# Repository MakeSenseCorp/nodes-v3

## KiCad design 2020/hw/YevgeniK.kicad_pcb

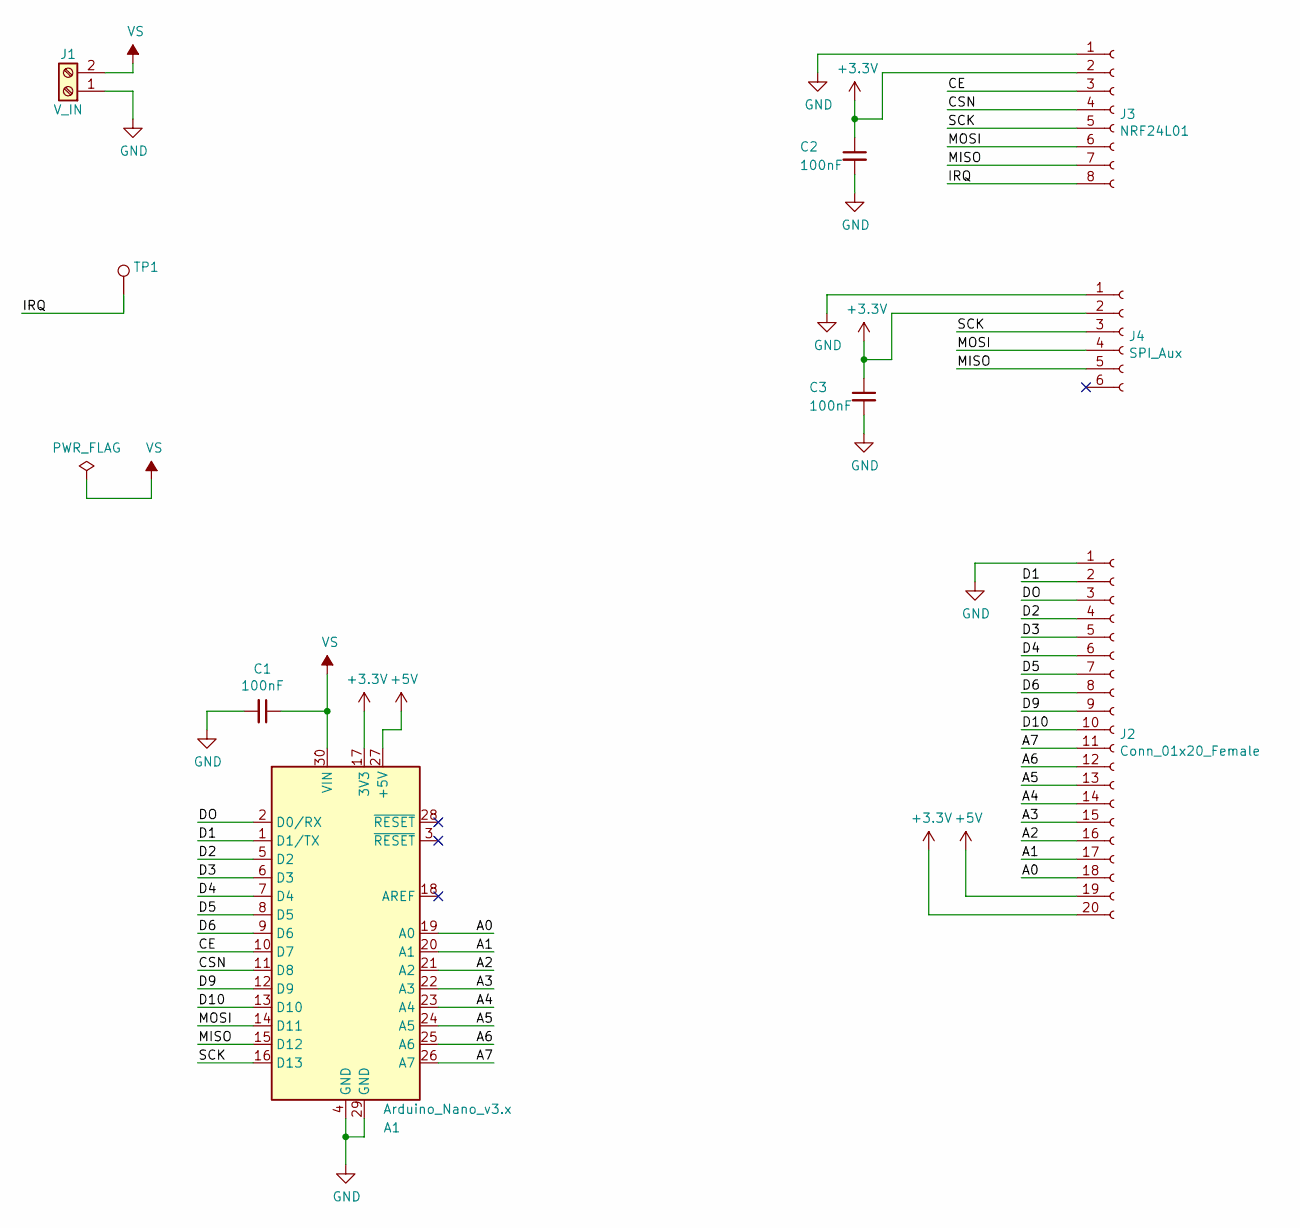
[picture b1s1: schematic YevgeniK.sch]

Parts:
A1: Arduino_Nano_v3.x; Arduino_Nano
C1, C2, C3: 100nF; C_0805_2012Metric
J1: V_IN; TerminalBlock_bornier-2_P5.08mm
J2: Conn_01x20_Female; PinHeader_1x20_P2.54mm_Vertical
J3: NRF24L01; PinHeader_2x04_P2.54mm_Vertical
J4: SPI_Aux; PinHeader_1x06_P2.54mm_Vertical
TP1: TestPoint; TestPoint_Pad_D2.0mm

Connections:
+3V3: A1.17 (3V3), C2.1, C3.1, J2.20, J3.2, J4.2
+5V: A1.27 (+5V), J2.19
/A0: A1.19 (A0), J2.18
/A1: A1.20 (A1), J2.17
/A2: A1.21 (A2), J2.16
/A3: A1.22 (A3), J2.15
/A4: A1.23 (A4), J2.14
/A5: A1.24 (A5), J2.13
/A6: A1.25 (A6), J2.12
/A7: A1.26 (A7), J2.11
/CE: A1.10 (D7), J3.3
/CSN: A1.11 (D8), J3.4
/D1: A1.1 (D1/TX), J2.2
/D2: A1.5 (D2), J2.4
/D3: A1.6 (D3), J2.5
/D4: A1.7 (D4), J2.6
/D5: A1.8 (D5), J2.7
/D6: A1.9 (D6), J2.8
/D9: A1.12 (D9), J2.9
/D10: A1.13 (D10), J2.10
/DO: A1.2 (D0/RX), J2.3
/IRQ: J3.8, TP1.1
/MISO: A1.15 (D12), J3.7, J4.5
/MOSI: A1.14 (D11), J3.6, J4.4
/SCK: A1.16 (D13), J3.5, J4.3
GND: A1.4 (GND), A1.29 (GND), C1.2, C2.2, C3.2, J1.1, J2.1, J3.1, J4.1
VS: A1.30 (VIN), C1.1, J1.2

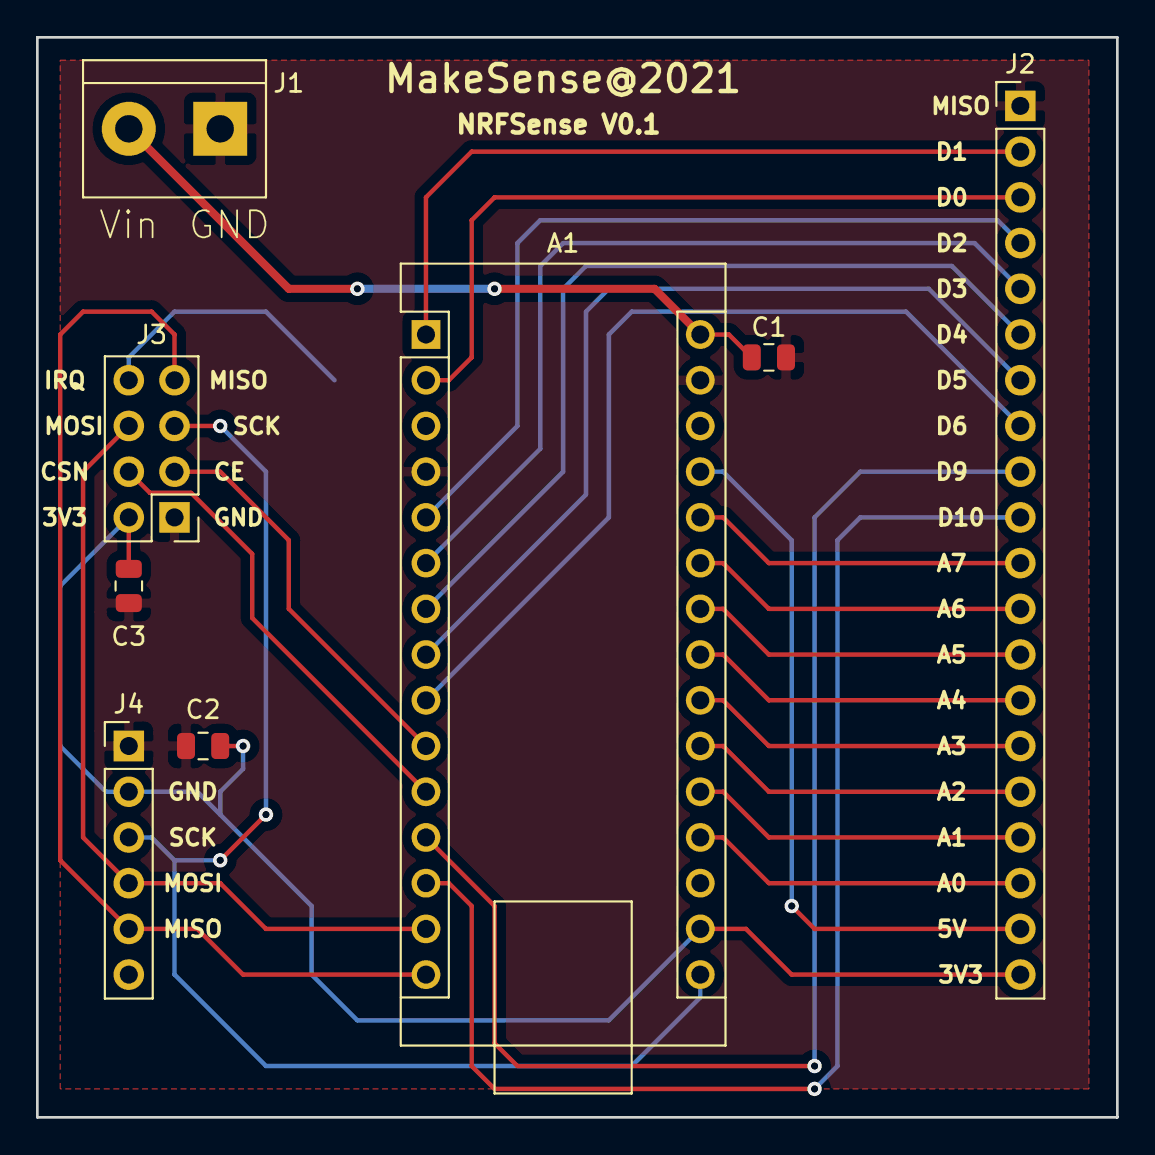
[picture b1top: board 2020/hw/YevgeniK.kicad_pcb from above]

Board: 2 copper layers, 60.0 x 60.0 mm, 9 parts (1 on the bottom side), 27 nets.

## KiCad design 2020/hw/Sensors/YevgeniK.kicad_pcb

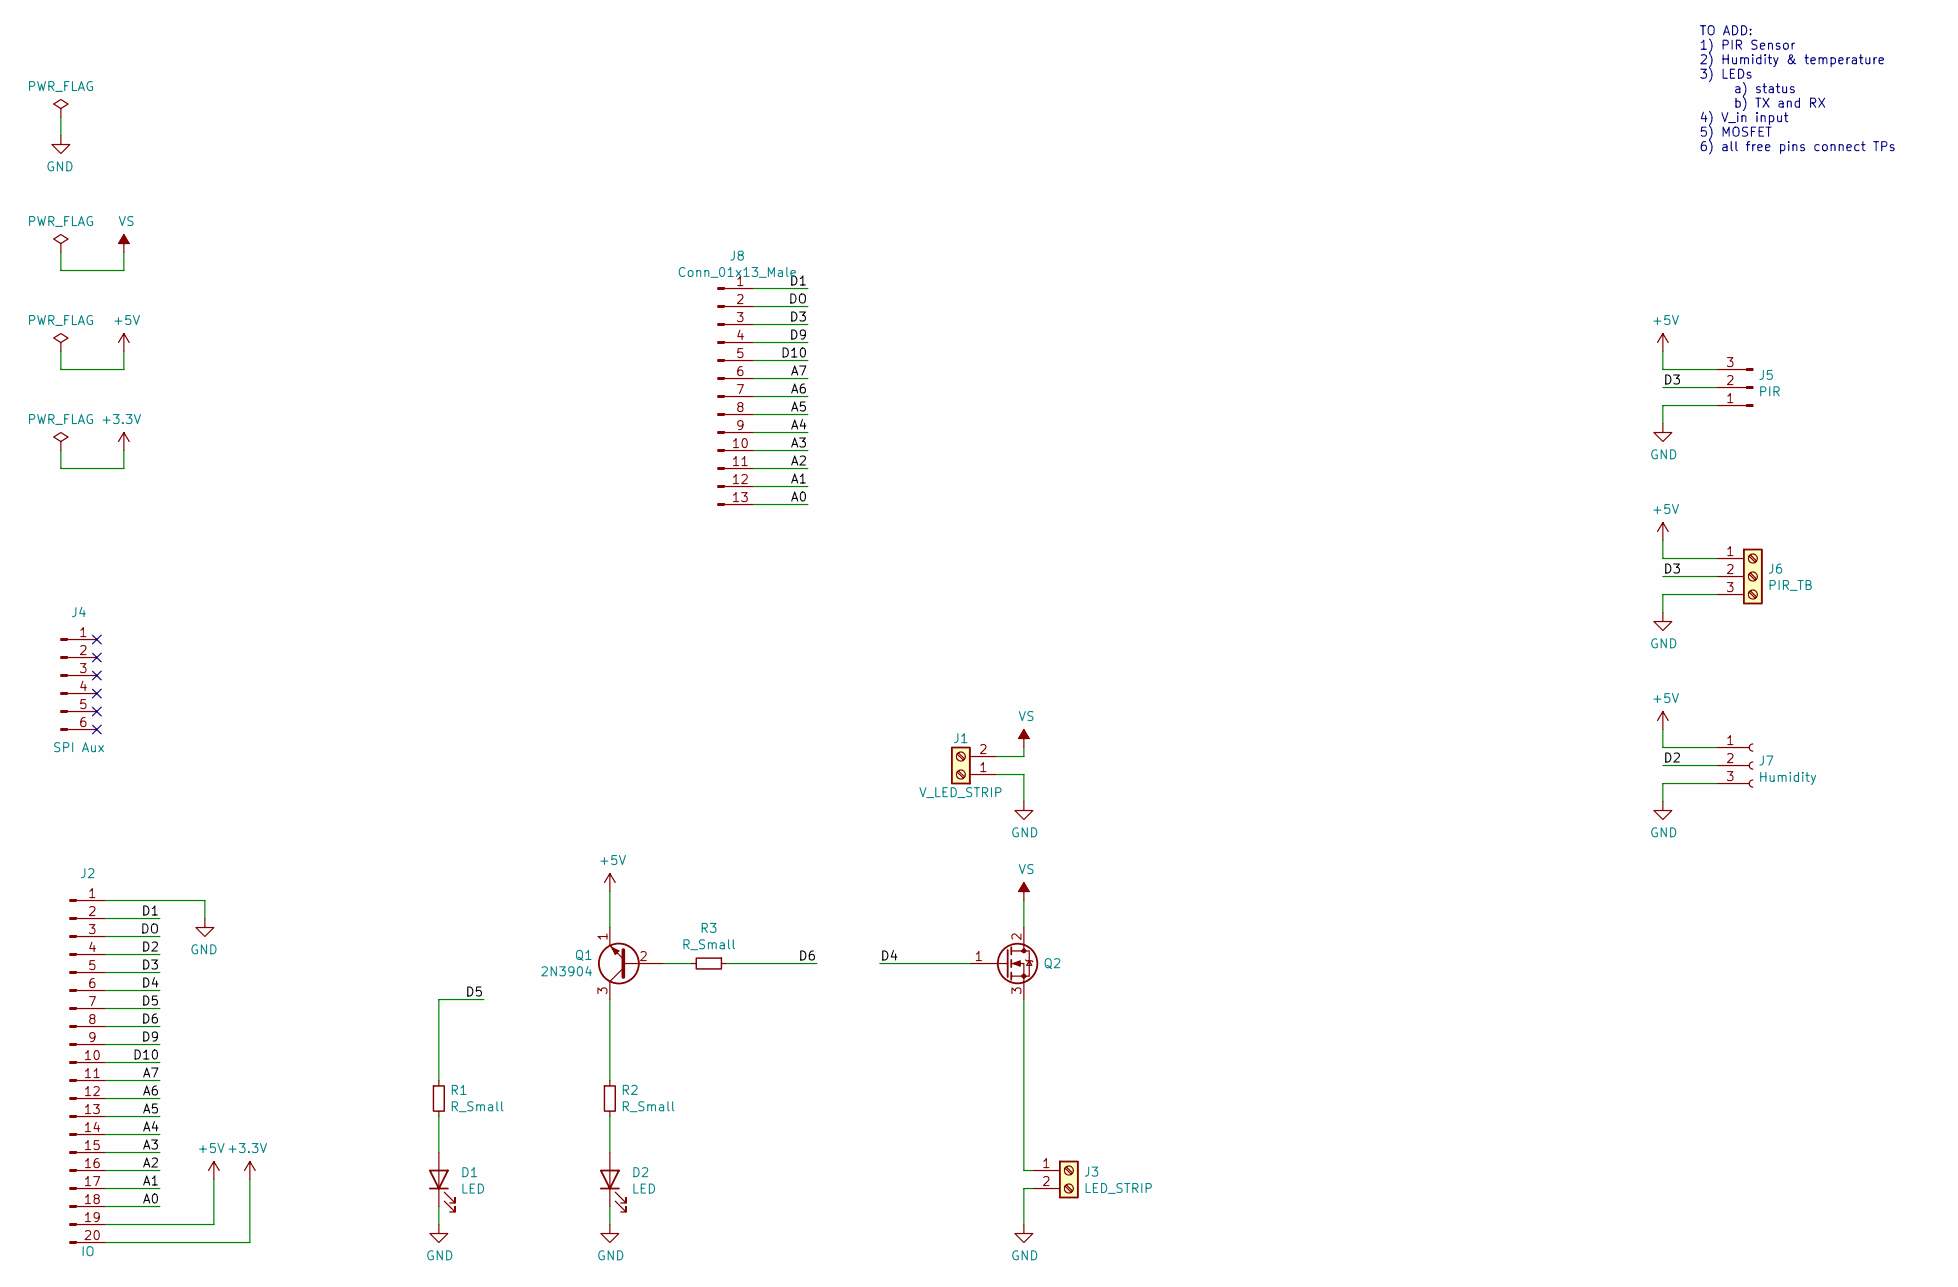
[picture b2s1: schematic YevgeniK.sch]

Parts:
D1, D2: LED; LED_D5.0mm_Clear
J1: V_LED_STRIP; TerminalBlock_bornier-2_P5.08mm
J2: IO; PinHeader_1x20_P2.54mm_Vertical
J3: LED_STRIP; TerminalBlock_bornier-2_P5.08mm
J4: SPI Aux; PinHeader_1x06_P2.54mm_Vertical
J5: PIR; PinHeader_1x03_P2.54mm_Vertical
J6: PIR_TB; TerminalBlock_bornier-3_P5.08mm
J7: Humidity; PinHeader_1x03_P2.54mm_Vertical
J8: Conn_01x13_Male; PinHeader_1x13_P2.54mm_Vertical
Q1: 2N3904; TO-92_Inline
Q2: Q_NMOS_GDS; TO-220-3_Horizontal_TabDown
R1, R2: R_Small; R_1206_3216Metric
R3: R_Small; R_0805_2012Metric

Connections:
+3V3: J2.20
+5V: J2.19, J5.3, J6.1, J7.1, Q1.1 (E)
/A0: J2.18, J8.13
/A1: J2.17, J8.12
/A2: J2.16, J8.11
/A3: J2.15, J8.10
/A4: J2.14, J8.9
/A5: J2.13, J8.8
/A6: J2.12, J8.7
/A7: J2.11, J8.6
/D1: J2.2, J8.1
/D2: J2.4, J7.2
/D3: J2.5, J5.2, J6.2, J8.3
/D4: J2.6, Q2.1 (G)
/D5: J2.7, R1.1
/D6: J2.8, R3.1
/D9: J2.9, J8.4
/D10: J2.10, J8.5
/DO: J2.3, J8.2
GND: D1.1 (K), D2.1 (K), J1.1, J2.1, J3.2, J5.1, J6.3, J7.3
unnamed: D1.2 (A), R1.2
unnamed: D2.2 (A), R2.2
unnamed: J3.1, Q2.3 (S)
unnamed: Q1.2 (B), R3.2
unnamed: Q1.3 (C), R2.1
VS: J1.2, Q2.2 (D)

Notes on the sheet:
TO ADD: 1) PIR Sensor 2) Humidity & temperature 3) LEDs a) status b) TX and RX 4) V_in input 5) MOSFET 6) all free pins connect TPs

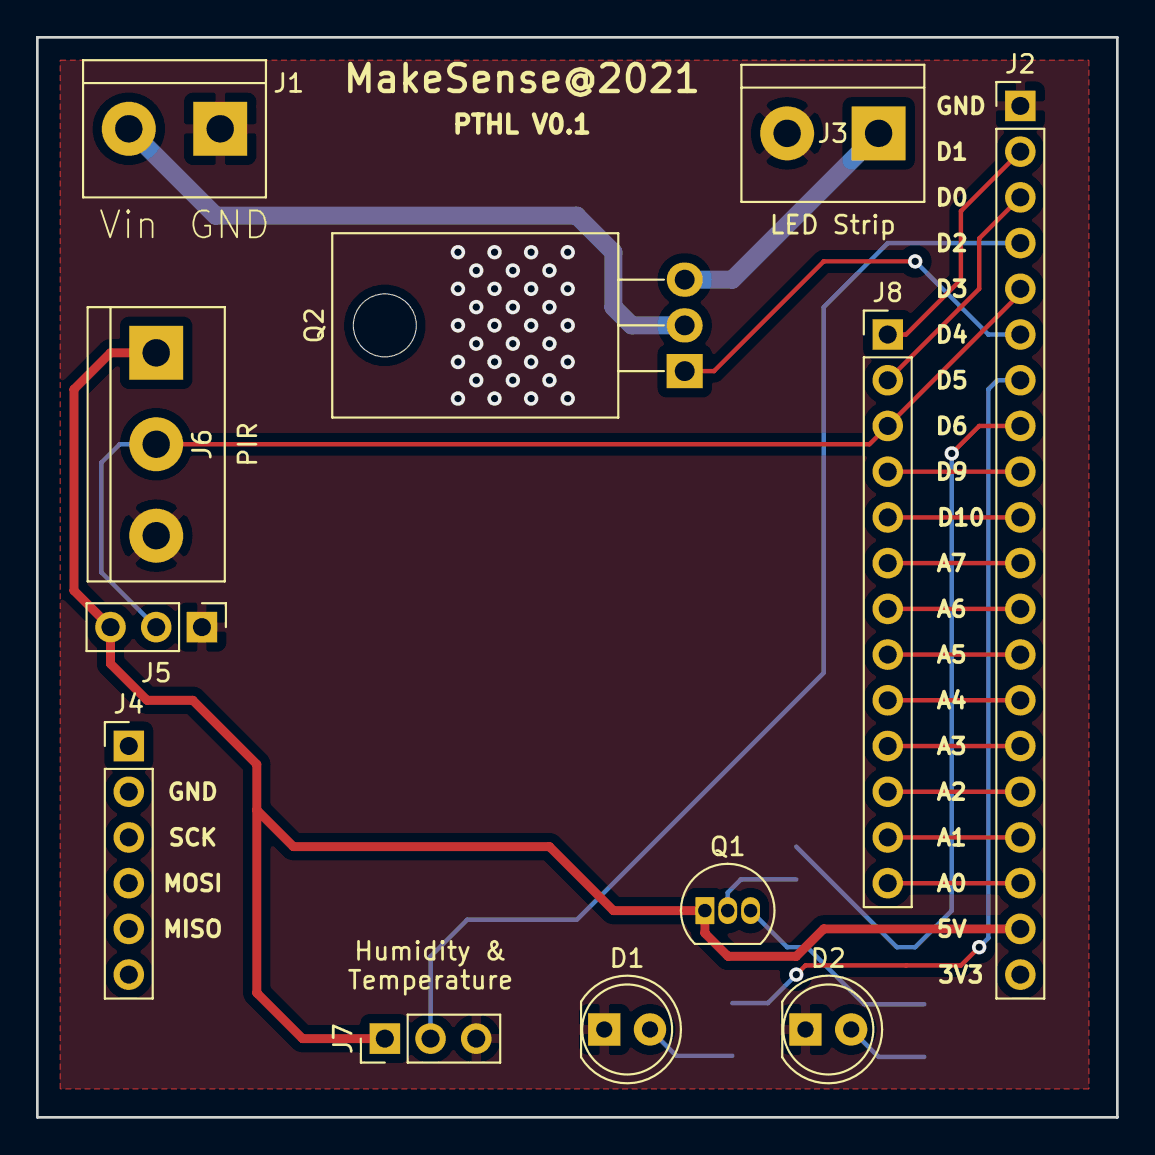
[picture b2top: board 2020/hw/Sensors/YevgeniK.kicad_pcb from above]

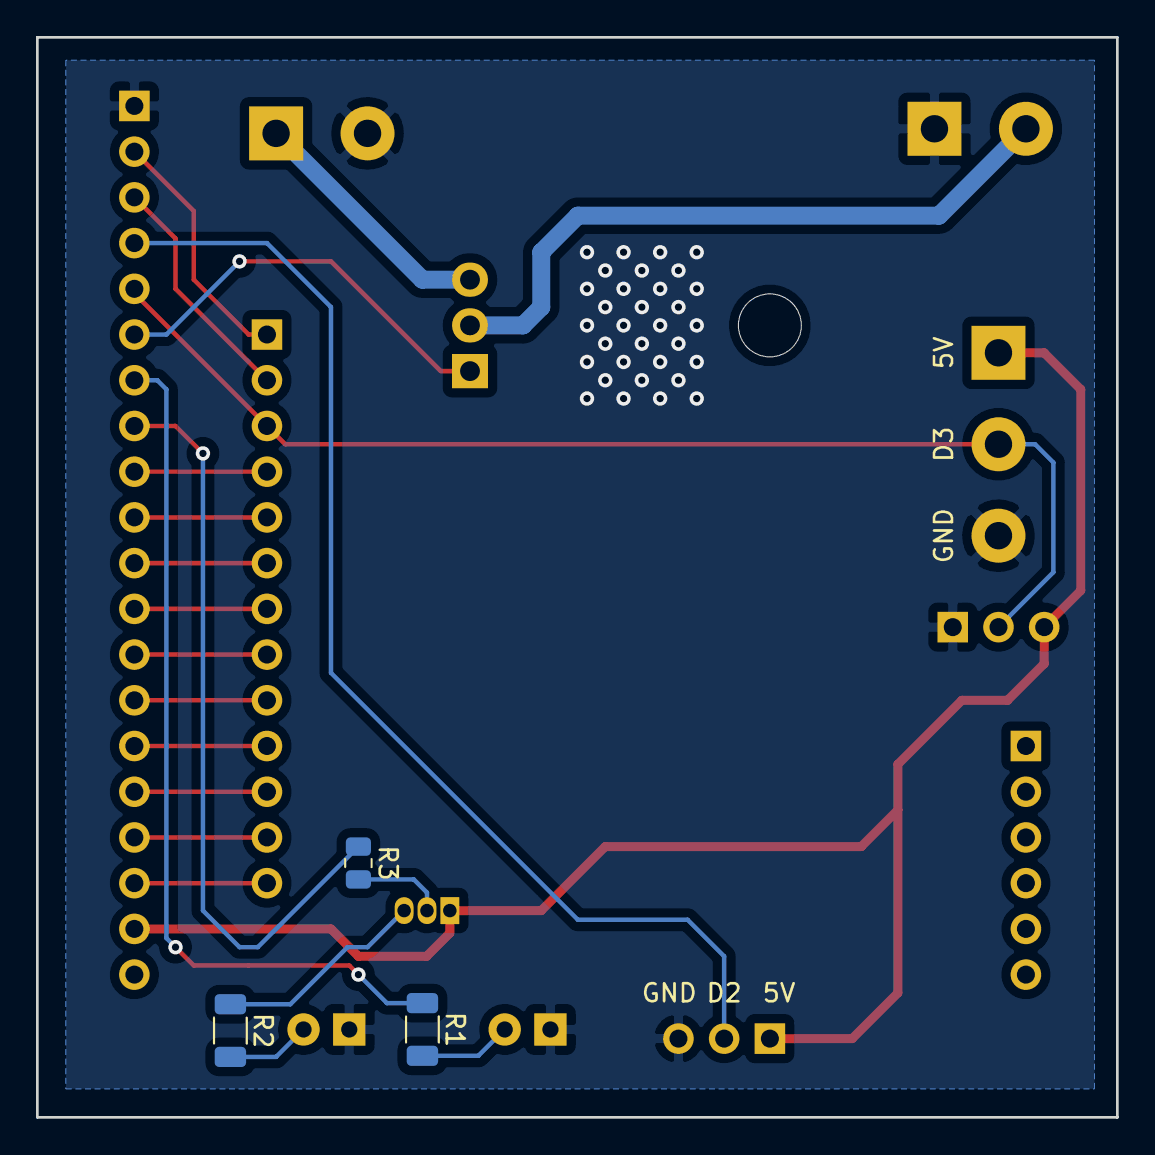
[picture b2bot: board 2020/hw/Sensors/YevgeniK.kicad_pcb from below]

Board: 2 copper layers, 60.0 x 60.0 mm, 15 parts (3 on the bottom side), 25 nets.

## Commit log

2020-12-08 python3 enable #1
2020-12-10 python 3 #2
2021-01-03 windows enable
2021-01-05 node ui misc info fix
2021-01-16 comnit
2021-01-23 new stock monitor node
2021-01-26 ui commit
2021-03-01 remove
2021-03-18 commit"
2021-04-06 prediction
2021-04-06 nasdaq class
2021-04-13 new 2023 (funder)
2021-04-18 new 2024 (stock db)
2021-04-27 comit
2021-05-23 window move
2021-06-07 window.py
2021-07-12 node 2020 (nrf sensors) poc
2021-07-13 poc cli for 2020 nrf relay working
2021-07-20 convert to python3
2021-07-27 node 2020 commit
2021-08-07 cli tool for stocks
2021-08-08 terminal added web
2021-08-12 nrf sensors architecture
2021-08-12 nrf module
2021-08-13 nrf fixes
2021-08-13 nrf set address update nrf hw address
2021-08-15 2022
2021-08-19 nrf commit
2021-08-22 nrf node
2021-08-22 stock node
2021-08-25 nrf async + more
2021-09-04 sensor_id to device_id
2021-09-05 nrf node first ui
2021-09-06 nrf node ui
2021-09-15 added jquery mobile to 2020 poc
